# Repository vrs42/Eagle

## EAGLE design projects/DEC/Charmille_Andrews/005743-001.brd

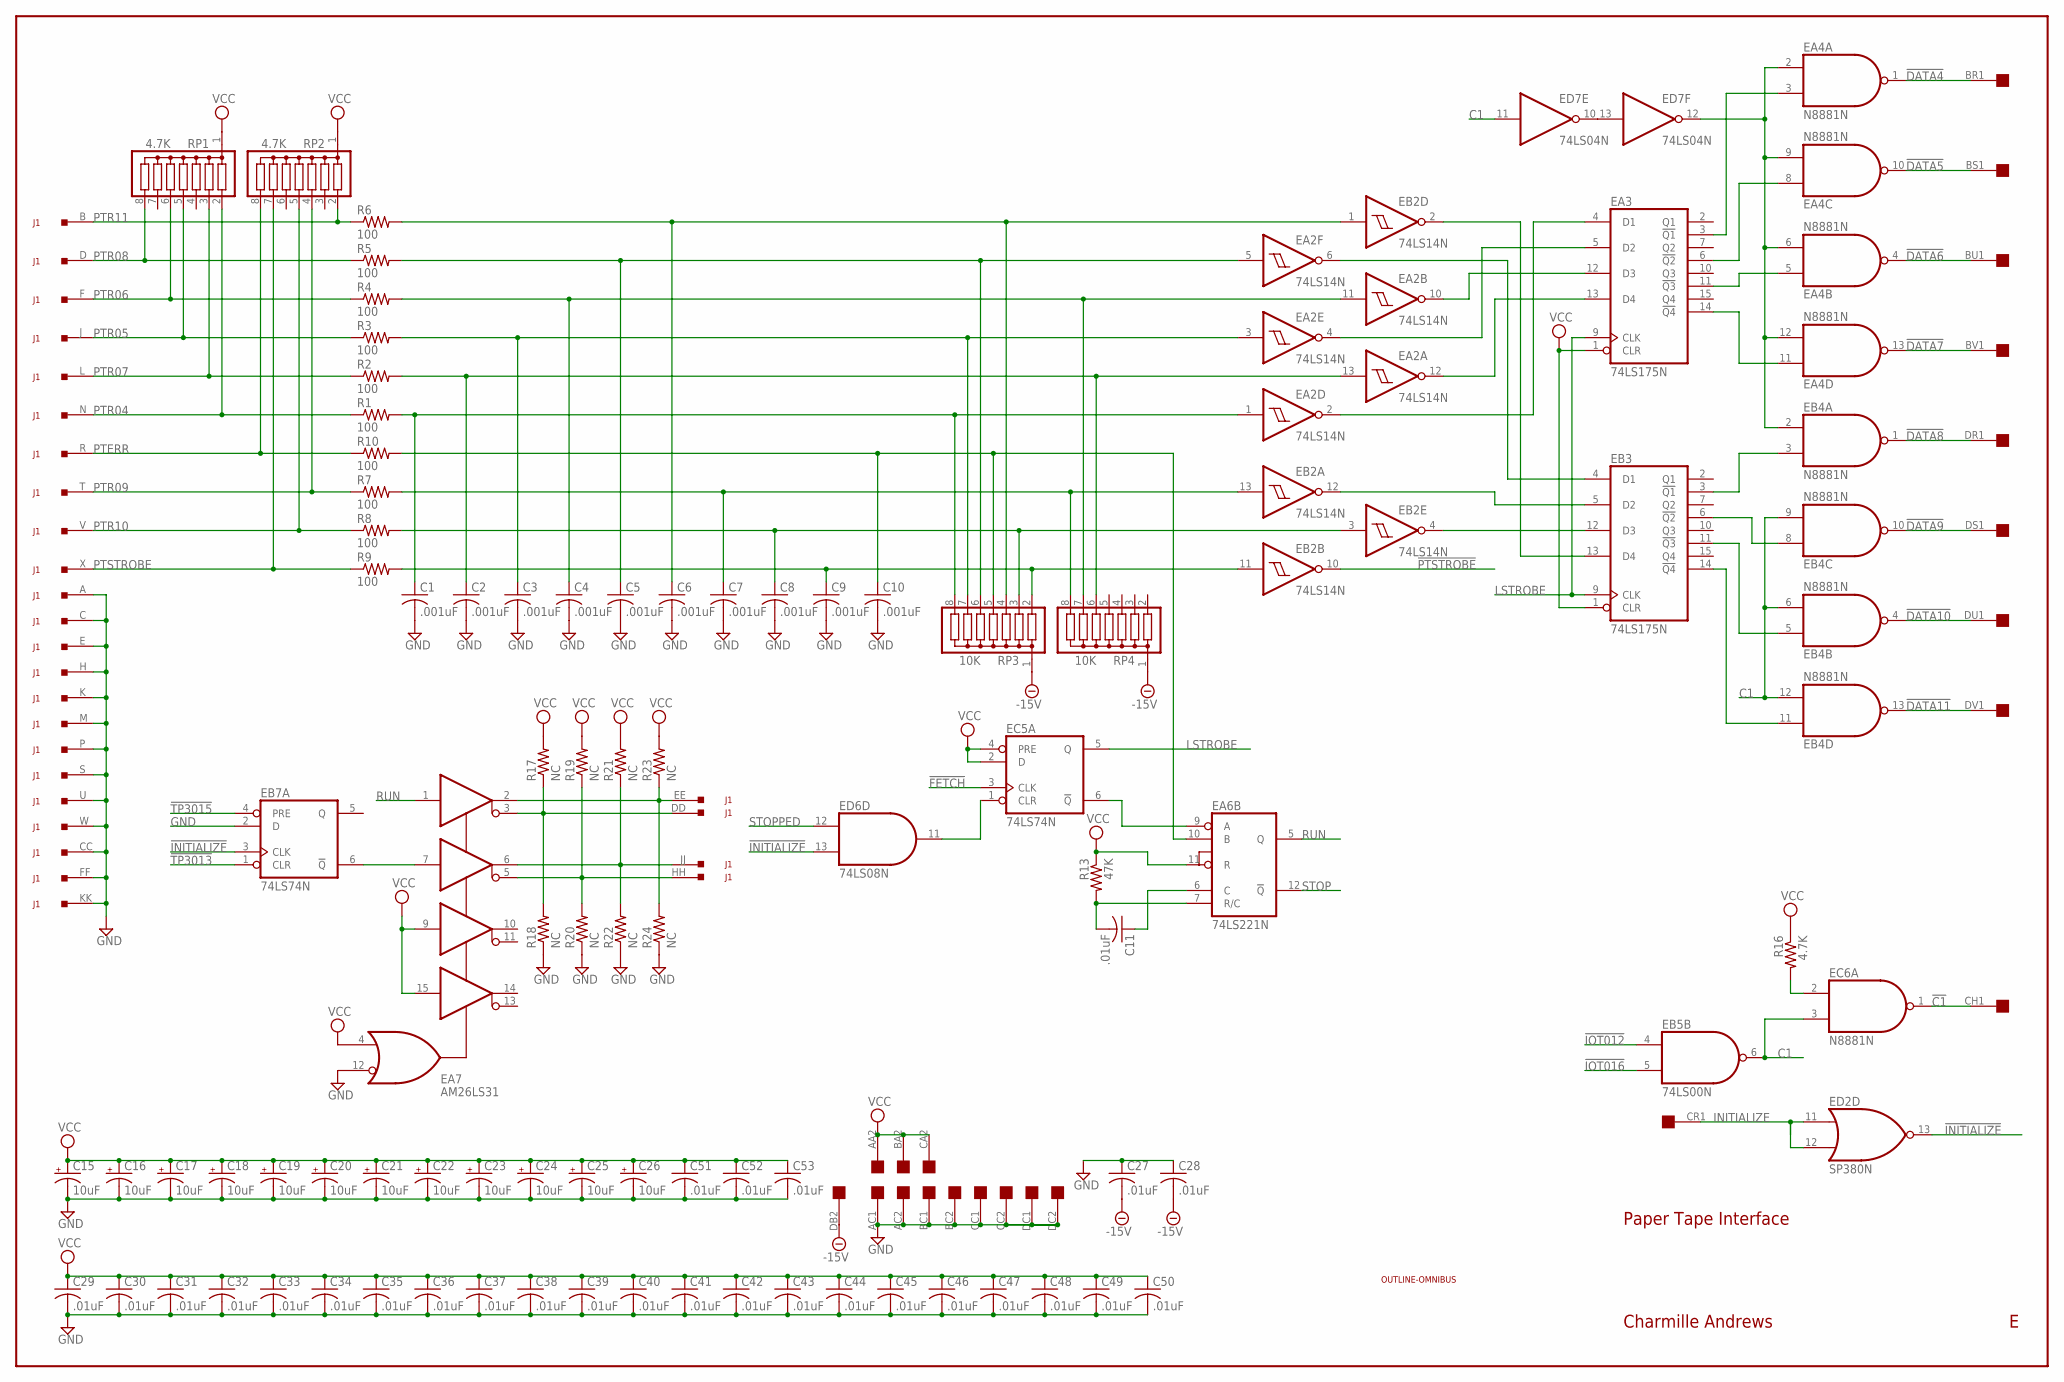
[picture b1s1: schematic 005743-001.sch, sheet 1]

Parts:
C1, C2, C3, C4, C5, C6, C7, C8, C9, C10: .001uF; C050-025X075
C11, C27, C28, C29, C30, C31, C32, C33, C34, C35, C36, C37, C38, C39, C40, C41, C42, C43, C44, C45, C46, C47, C48, C49, C50, C51, C52, C53: .01uF; C050-025X075
C15, C16, C17, C18, C19, C20, C21, C22, C23, C24, C25, C26: 10uF; E15-5
EA2: 74LS14N; DIL14
EA3: 74LS175N; DIL16
EA4: N8881N; DIL14
EA6: 74LS221N; DIL16
EA7: AM26LS31; DIL16
EB2: 74LS14N; DIL14
EB3: 74LS175N; DIL16
EB4: N8881N; DIL14
EB5: 74LS00N; DIL14
EB7: 74LS74N; DIL14
EC5: 74LS74N; DIL14
EC6: N8881N; DIL14
ED2: SP380N; DIL14
ED6: 74LS08N; DIL14
ED7: 74LS04N; DIL14
J1: DEC40PINSH; DEC40PINH
R1, R2, R3, R4, R5, R6, R7, R8, R9, R10: 100; 0207/12
R13: 47K; 0207/12
R16: 4.7K; 0207/12
R17, R18, R19, R20, R21, R22, R23, R24: NC; 0207/12
RP1, RP2: 4.7K; SIL8
RP3, RP4: 10K; SIL8
U$1: OUTLINE-OMNIBUS; OMNIBUS
U$2: QUAD; EDGE-CON8

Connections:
!C1: EC6.1 (O), U$2.CH1
!DATA4: EA4.1 (O), U$2.BR1
!DATA5: EA4.10 (O), U$2.BS1
!DATA6: EA4.4 (O), U$2.BU1
!DATA7: EA4.13 (O), U$2.BV1
!DATA8: EB4.1 (O), U$2.DR1
!DATA9: EB4.10 (O), U$2.DS1
!DATA10: EB4.4 (O), U$2.DU1
!DATA11: EB4.13 (O), U$2.DV1
!FETCH: EC5.3 (CLK); also elsewhere on the board
!INITIALIZE: EB7.3 (CLK), ED2.13 (O), ED6.13 (I1); also elsewhere on the board
!IOT012: EB5.4 (I0); also elsewhere on the board
!IOT016: EB5.5 (I1); also elsewhere on the board
!PTSTROBE: EB2.10 (O); also elsewhere on the board
!TP3013: EB7.1 (CLR); also elsewhere on the board
!TP3015: EB7.4 (PRE); also elsewhere on the board
-15V: C27.2, C28.2, RP3.1, RP4.1, U$2.DB2
C1: EB4.6 (I1), EB4.9 (I1), EB4.12 (I1), EB5.6 (O), EC6.3 (I1), ED7.11 (I)
GND: C1.2, C2.2, C3.2, C4.2, C5.2, C6.2, C7.2, C8.2, C9.2, C10.2, C15.-, C16.-, C17.-, C18.-, C19.-, C20.-, C21.-, C22.-, C23.-, C24.-, C25.-, C26.-, C27.1, C28.1, C29.2, C30.2, C31.2, C32.2, C33.2, C34.2, C35.2, C36.2, C37.2, C38.2, C39.2, C40.2, C41.2, C42.2, C43.2, C44.2, C45.2, C46.2, C47.2, C48.2, C49.2, C50.2, C51.2, C52.2, C53.2, EA2.7 (GND), EA3.8 (GND), EA4.7 (GND), EA6.8 (GND), EA7.8 (GND), EA7.12 (!G), EB2.7 (GND), EB3.8 (GND), EB4.7 (GND), EB5.7 (GND), EB7.2 (D), EB7.7 (GND), EC5.7 (GND), EC6.7 (GND), ED2.1 (GND), ED6.7 (GND), ED7.7 (GND), J1.A, J1.C, J1.CC, J1.E, J1.FF, J1.H, J1.K, J1.KK, J1.M, J1.P, J1.S, J1.U, J1.W, R18.1, R20.1, R22.1, R24.1, U$2.AC1, U$2.AC2, U$2.BC1, U$2.BC2, U$2.CC1, U$2.CC2, U$2.DC1, U$2.DC2; also elsewhere on the board
INITIALIZE: ED2.11 (I0), ED2.12 (I1), U$2.CR1
LSTROBE: EA3.9 (CLK), EB3.9 (CLK), EC5.5 (Q); also elsewhere on the board
unnamed: EA4.2 (I0), EA4.6 (I1), EA4.9 (I1), EA4.12 (I1), EB4.2 (I0), ED7.12 (O)
unnamed: EA2.6 (O), EB3.4 (D1)
unnamed: ED7.10 (O), ED7.13 (I)
unnamed: EA7.2 (Y1), J1.EE, R23.1, R24.2
unnamed: EA7.3 (Z1), J1.DD, R17.1, R18.2
unnamed: EC5.1 (CLR), ED6.11 (O)
unnamed: EA7.5 (Z2), J1.HH, R19.1, R20.2
unnamed: EA7.6 (Y2), J1.JJ, R21.1, R22.2
unnamed: EB2.2 (O), EB3.13 (D4)
unnamed: EA2.12 (O), EA3.13 (D4)
unnamed: EA7.7 (A2), EB7.6 (!Q)
unnamed: EA2.10 (O), EA3.12 (D3)
unnamed: EA3.6 (!Q2), EA4.8 (I0)
unnamed: EA6.9 (A), EC5.6 (!Q)
unnamed: EC6.2 (I0), R16.2
unnamed: C10.1, EA6.10 (B), R10.2, RP3.5
unnamed: C11.1, EA6.6 (C)
unnamed: EA2.2 (O), EA3.4 (D1)
unnamed: EA3.3 (!Q1), EA4.3 (I1)
unnamed: EA3.14 (!Q4), EA4.11 (I0)
unnamed: C11.2, EA6.7 (R/C), R13.2
unnamed: EB3.14 (!Q4), EB4.11 (I0)
unnamed: EB3.6 (!Q2), EB4.8 (I0)
unnamed: EB3.11 (!Q3), EB4.5 (I0)
unnamed: EB3.3 (!Q1), EB4.3 (I1)
unnamed: EB2.12 (O), EB3.5 (D2)
unnamed: EB2.4 (O), EB3.12 (D3)
unnamed: C7.1, EB2.13 (I), R7.2, RP4.8
unnamed: C8.1, EB2.3 (I), R8.2, RP3.3
unnamed: C6.1, EB2.1 (I), R6.2, RP3.4
unnamed: C9.1, EB2.11 (I), R9.2, RP3.2
unnamed: EA3.11 (!Q3), EA4.5 (I0)
unnamed: EA2.4 (O), EA3.5 (D2)
unnamed: C2.1, EA2.13 (I), R2.2, RP4.6
unnamed: C5.1, EA2.5 (I), R5.2, RP3.6
unnamed: C3.1, EA2.3 (I), R3.2, RP3.7
unnamed: C1.1, EA2.1 (I), R1.2, RP3.8
unnamed: C4.1, EA2.11 (I), R4.2, RP4.7
PTERR: J1.R, R10.1, RP2.8
PTR04: J1.N, R1.1, RP1.2
PTR05: J1.J, R3.1, RP1.5
PTR06: J1.F, R4.1, RP1.6
PTR07: J1.L, R2.1, RP1.3
PTR08: J1.D, R5.1, RP1.8
PTR09: J1.T, R7.1, RP2.4
PTR10: J1.V, R8.1, RP2.5
PTR11: J1.B, R6.1, RP2.2
PTSTROBE: J1.X, R9.1, RP2.7
RUN: EA6.5 (Q), EA7.1 (A1); also elsewhere on the board
STOP: EA6.12 (!Q); also elsewhere on the board
STOPPED: ED6.12 (I0); also elsewhere on the board
VCC: C15.+, C16.+, C17.+, C18.+, C19.+, C20.+, C21.+, C22.+, C23.+, C24.+, C25.+, C26.+, C29.1, C30.1, C31.1, C32.1, C33.1, C34.1, C35.1, C36.1, C37.1, C38.1, C39.1, C40.1, C41.1, C42.1, C43.1, C44.1, C45.1, C46.1, C47.1, C48.1, C49.1, C50.1, C51.1, C52.1, C53.1, EA2.14 (VCC), EA3.1 (CLR), EA3.16 (VCC), EA4.14 (VCC), EA6.11 (R), EA6.16 (VCC), EA7.4 (G), EA7.9 (A3), EA7.15 (A4), EA7.16 (VCC), EB2.14 (VCC), EB3.1 (CLR), EB3.16 (VCC), EB4.14 (VCC), EB5.14 (VCC), EB7.14 (VCC), EC5.2 (D), EC5.4 (PRE), EC5.14 (VCC), EC6.14 (VCC), ED2.8 (VCC), ED6.14 (VCC), ED7.14 (VCC), R13.1, R16.1, R17.2, R19.2, R21.2, R23.2, RP1.1, RP2.1, U$2.AA2, U$2.BA2, U$2.CA2; also elsewhere on the board

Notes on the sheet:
Paper Tape Interface
Charmille Andrews

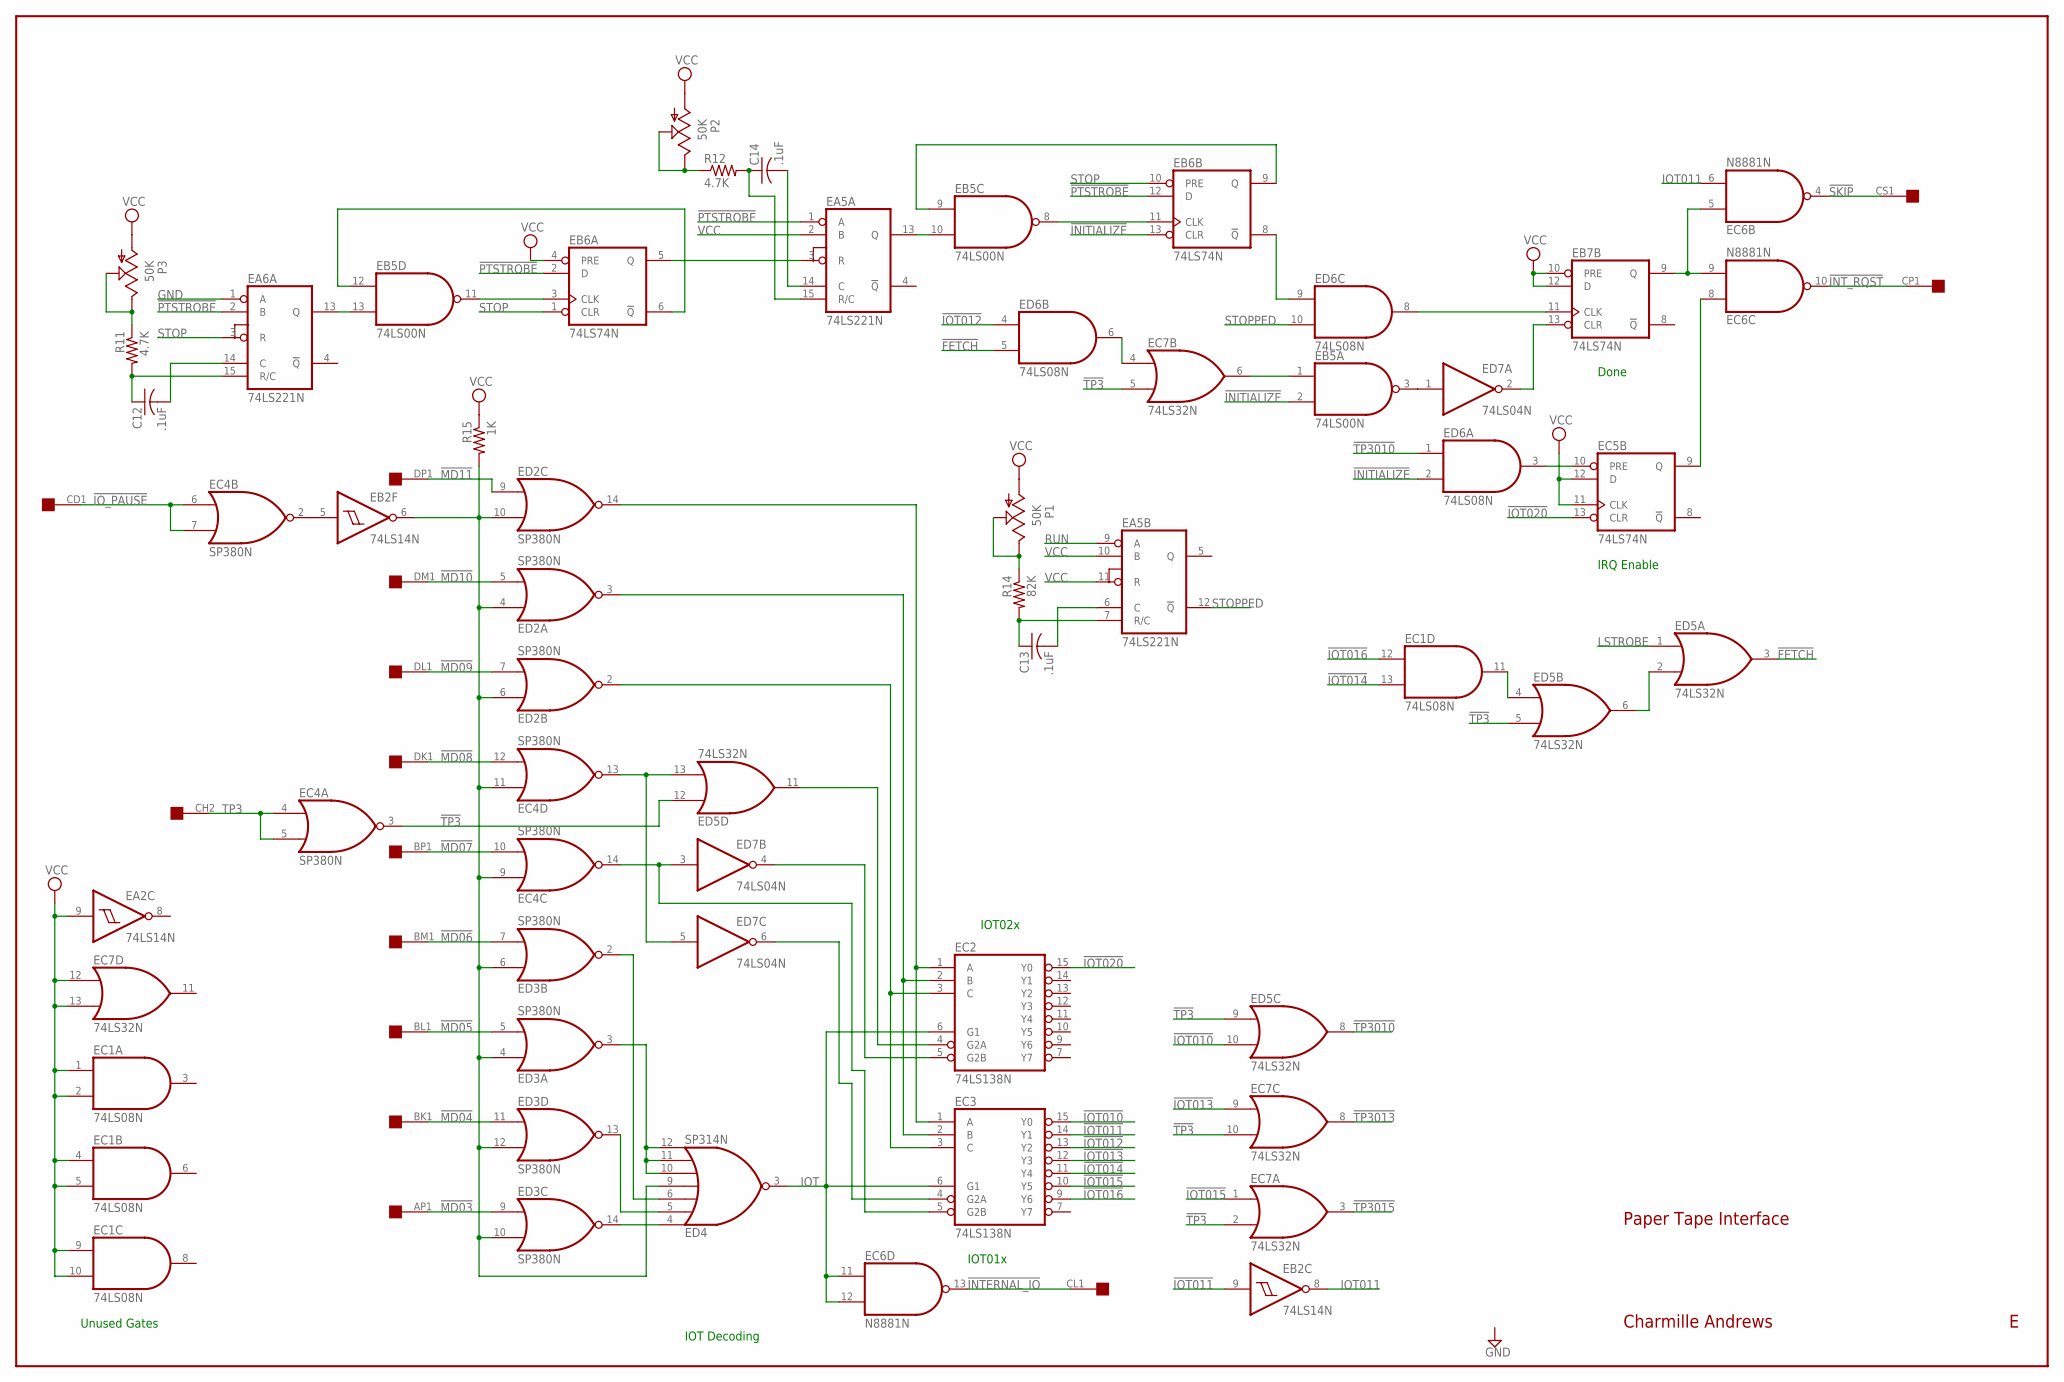
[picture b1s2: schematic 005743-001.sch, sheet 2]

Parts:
C12, C13, C14: .1uF; C150-054X183
EA2: 74LS14N; DIL14
EA5, EA6: 74LS221N; DIL16
EB2: 74LS14N; DIL14
EB5: 74LS00N; DIL14
EB6, EB7: 74LS74N; DIL14
EC1: 74LS08N; DIL14
EC2, EC3: 74LS138N; DIL16
EC4: SP380N; DIL14
EC5: 74LS74N; DIL14
EC6: N8881N; DIL14
EC7: 74LS32N; DIL14
ED2, ED3: SP380N; DIL14
ED4: SP314N; DIL14
ED5: 74LS32N; DIL14
ED6: 74LS08N; DIL14
ED7: 74LS04N; DIL14
P1, P2, P3: 50K; SP19L
R11, R12: 4.7K; 0207/12
R14: 82K; 0207/12
R15: 1K; 0207/12
U$2: QUAD; EDGE-CON8

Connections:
!FETCH: ED5.3 (O), ED6.5 (I1); also elsewhere on the board
!INITIALIZE: EB5.2 (I1), EB6.13 (CLR), ED6.2 (I1); also elsewhere on the board
!INTERNAL_IO: EC6.13 (O), U$2.CL1
!INT_RQST: EC6.10 (O), U$2.CP1
!IOT010: EC3.15 (Y0), ED5.10 (I1)
!IOT011: EB2.9 (I), EC3.14 (Y1)
!IOT012: EC3.13 (Y2), ED6.4 (I0); also elsewhere on the board
!IOT013: EC3.12 (Y3), EC7.9 (I0)
!IOT014: EC1.13 (I1), EC3.11 (Y4)
!IOT015: EC3.10 (Y5), EC7.1 (I0)
!IOT016: EC1.12 (I0), EC3.9 (Y6); also elsewhere on the board
!IOT020: EC2.15 (Y0), EC5.13 (CLR)
!IO_PAUSE: EC4.6 (I0), EC4.7 (I1), U$2.CD1
!MD03: ED3.9 (I0), U$2.AP1
!MD04: ED3.11 (I0), U$2.BK1
!MD05: ED3.5 (I1), U$2.BL1
!MD06: ED3.7 (I1), U$2.BM1
!MD07: EC4.10 (I1), U$2.BP1
!MD08: EC4.12 (I1), U$2.DK1
!MD09: ED2.7 (I1), U$2.DL1
!MD10: ED2.5 (I1), U$2.DM1
!MD11: ED2.9 (I0), U$2.DP1
!PTSTROBE: EA5.1 (A), EA6.2 (B), EB6.2 (D), EB6.12 (D); also elsewhere on the board
!SKIP: EC6.4 (O), U$2.CS1
!TP3: EC4.3 (O), EC7.2 (I1), EC7.5 (I1), EC7.10 (I1), ED5.5 (I1), ED5.9 (I0), ED5.12 (I0)
!TP3010: ED5.8 (O), ED6.1 (I0)
!TP3013: EC7.8 (O); also elsewhere on the board
!TP3015: EC7.3 (O); also elsewhere on the board
GND: EA2.7 (GND), EA5.8 (GND), EA6.1 (A), EA6.8 (GND), EB2.7 (GND), EB5.7 (GND), EB6.7 (GND), EB7.7 (GND), EC1.7 (GND), EC2.8 (GND), EC3.8 (GND), EC4.1 (GND), EC5.7 (GND), EC6.7 (GND), EC7.7 (GND), ED2.1 (GND), ED3.1 (GND), ED4.1 (GND), ED5.7 (GND), ED6.7 (GND), ED7.7 (GND); also elsewhere on the board
IOT: EC2.6 (G1), EC3.6 (G1), EC6.11 (I0), EC6.12 (I1), ED4.3 (O)
IOT011: EB2.8 (O), EC6.6 (I1)
LSTROBE: ED5.1 (I0); also elsewhere on the board
unnamed: EB5.3 (O), ED7.1 (I)
unnamed: EC4.13 (O), ED5.13 (I1), ED7.5 (I)
unnamed: EC3.5 (G2B), EC4.14 (O), ED7.3 (I)
unnamed: EB7.13 (CLR), ED7.2 (O)
unnamed: EC3.4 (G2A), ED7.6 (O)
unnamed: EB7.11 (CLK), ED6.8 (O)
unnamed: EB6.8 (!Q), ED6.9 (I0)
unnamed: EC5.10 (PRE), ED6.3 (O)
unnamed: EC7.4 (I0), ED6.6 (O)
unnamed: C12.2, EA6.14 (C)
unnamed: C14.1, EA5.15 (R/C), R12.2
unnamed: EA5.3 (R), EB6.5 (Q)
unnamed: EC1.11 (O), ED5.4 (I0)
unnamed: ED5.2 (I1), ED5.6 (O)
unnamed: EA6.13 (Q), EB5.13 (I1)
unnamed: EC2.4 (G2A), ED5.11 (O)
unnamed: ED3.14 (O), ED4.4 (I0)
unnamed: ED3.3 (O), ED4.10 (I4), ED4.11 (I5), ED4.12 (I6)
unnamed: EB2.6 (O), EC4.9 (I0), EC4.11 (I0), ED2.4 (I0), ED2.6 (I0), ED2.10 (I1), ED3.4 (I0), ED3.6 (I0), ED3.10 (I1), ED3.12 (I1), ED4.9 (I3), R15.2
unnamed: ED3.2 (O), ED4.6 (I2)
unnamed: ED3.13 (O), ED4.5 (I1)
unnamed: EB2.5 (I), EC4.2 (O)
unnamed: EC2.1 (A), EC3.1 (A), ED2.14 (O)
unnamed: EC2.5 (G2B), ED7.4 (O)
unnamed: EC2.2 (B), EC3.2 (B), ED2.3 (O)
unnamed: EC2.3 (C), EC3.3 (C), ED2.2 (O)
unnamed: EB7.9 (Q), EC6.5 (I0), EC6.9 (I1)
unnamed: EC5.9 (Q), EC6.8 (I0)
unnamed: EB5.1 (I0), EC7.6 (O)
unnamed: EB5.8 (O), EB6.11 (CLK)
unnamed: EB5.9 (I0), EB6.9 (Q)
unnamed: EB5.11 (O), EB6.3 (CLK)
unnamed: EB5.12 (I0), EB6.6 (!Q)
unnamed: EA5.13 (Q), EB5.10 (I1)
unnamed: C12.1, EA6.15 (R/C), R11.2
unnamed: C13.2, EA5.6 (C)
unnamed: C13.1, EA5.7 (R/C), R14.2
unnamed: C14.2, EA5.14 (C)
unnamed: P1.E, P1.S, R14.1
unnamed: P2.E, P2.S, R12.1
unnamed: P3.E, P3.S, R11.1
RUN: EA5.9 (A); also elsewhere on the board
STOP: EA6.3 (R), EB6.1 (CLR), EB6.10 (PRE); also elsewhere on the board
STOPPED: EA5.12 (!Q), ED6.10 (I1); also elsewhere on the board
TP3: EC4.4 (I0), EC4.5 (I1), U$2.CH2
VCC: EA2.9 (I), EA2.14 (VCC), EA5.2 (B), EA5.10 (B), EA5.11 (R), EA5.16 (VCC), EA6.16 (VCC), EB2.14 (VCC), EB5.14 (VCC), EB6.4 (PRE), EB6.14 (VCC), EB7.10 (PRE), EB7.12 (D), EB7.14 (VCC), EC1.1 (I0), EC1.2 (I1), EC1.4 (I0), EC1.5 (I1), EC1.9 (I0), EC1.10 (I1), EC1.14 (VCC), EC2.16 (VCC), EC3.16 (VCC), EC4.8 (VCC), EC5.11 (CLK), EC5.12 (D), EC5.14 (VCC), EC6.14 (VCC), EC7.12 (I0), EC7.13 (I1), EC7.14 (VCC), ED2.8 (VCC), ED3.8 (VCC), ED4.8 (VCC), ED5.14 (VCC), ED6.14 (VCC), ED7.14 (VCC), P1.A, P2.A, P3.A, R15.1; also elsewhere on the board

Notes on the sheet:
IOT02x
IOT01x
IOT Decoding
Unused Gates
IRQ Enable
Done
Paper Tape Interface
Charmille Andrews

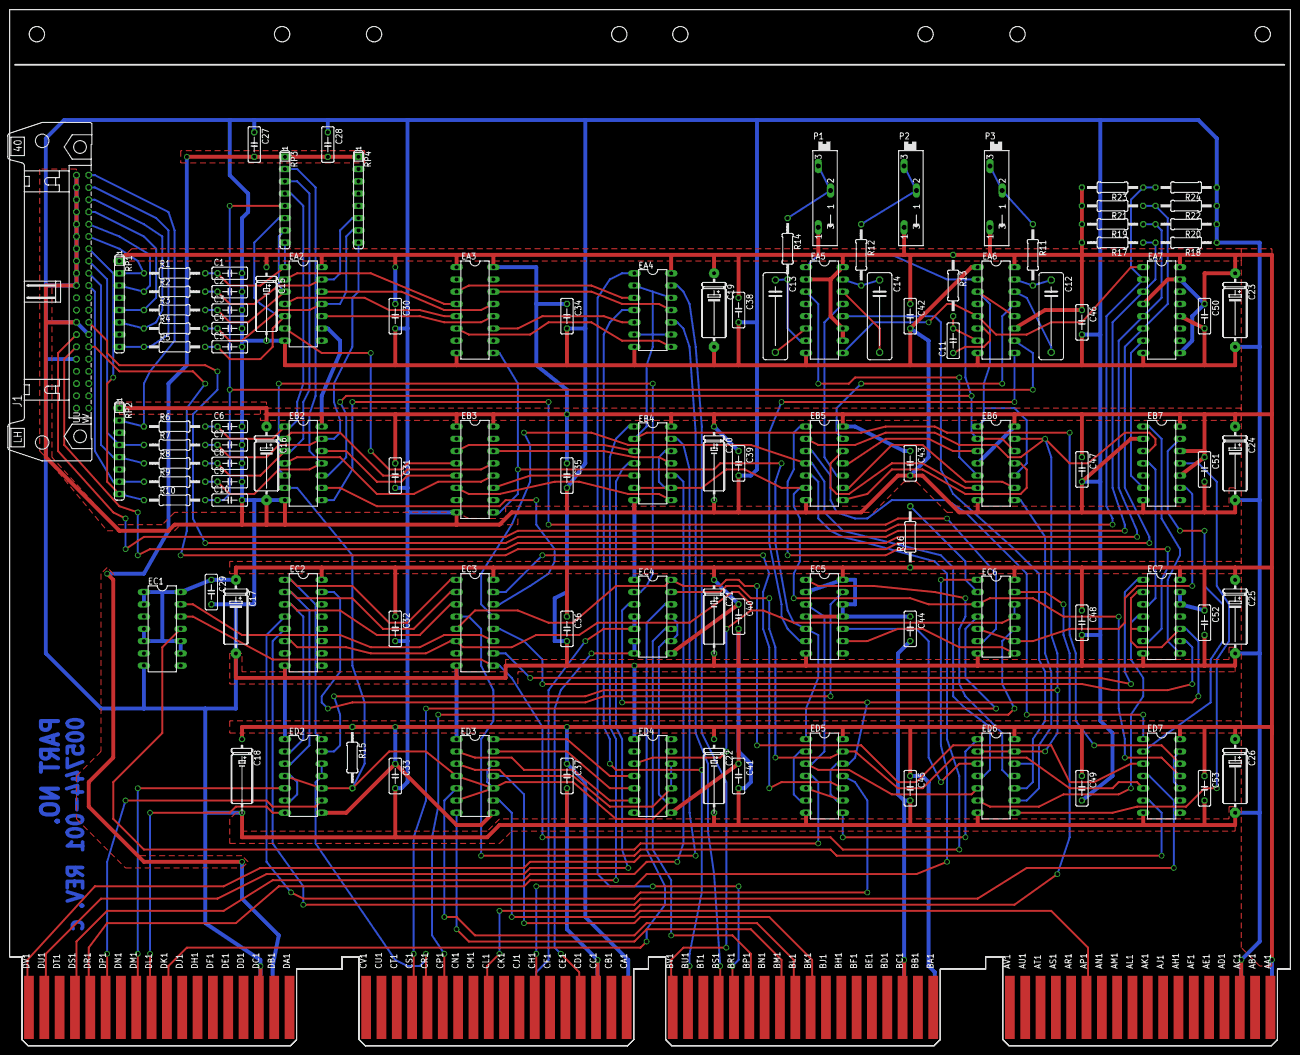
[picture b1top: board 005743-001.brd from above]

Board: 2 copper layers, 265.3 x 214.6 mm, 112 parts (0 on the bottom side), 138 nets.

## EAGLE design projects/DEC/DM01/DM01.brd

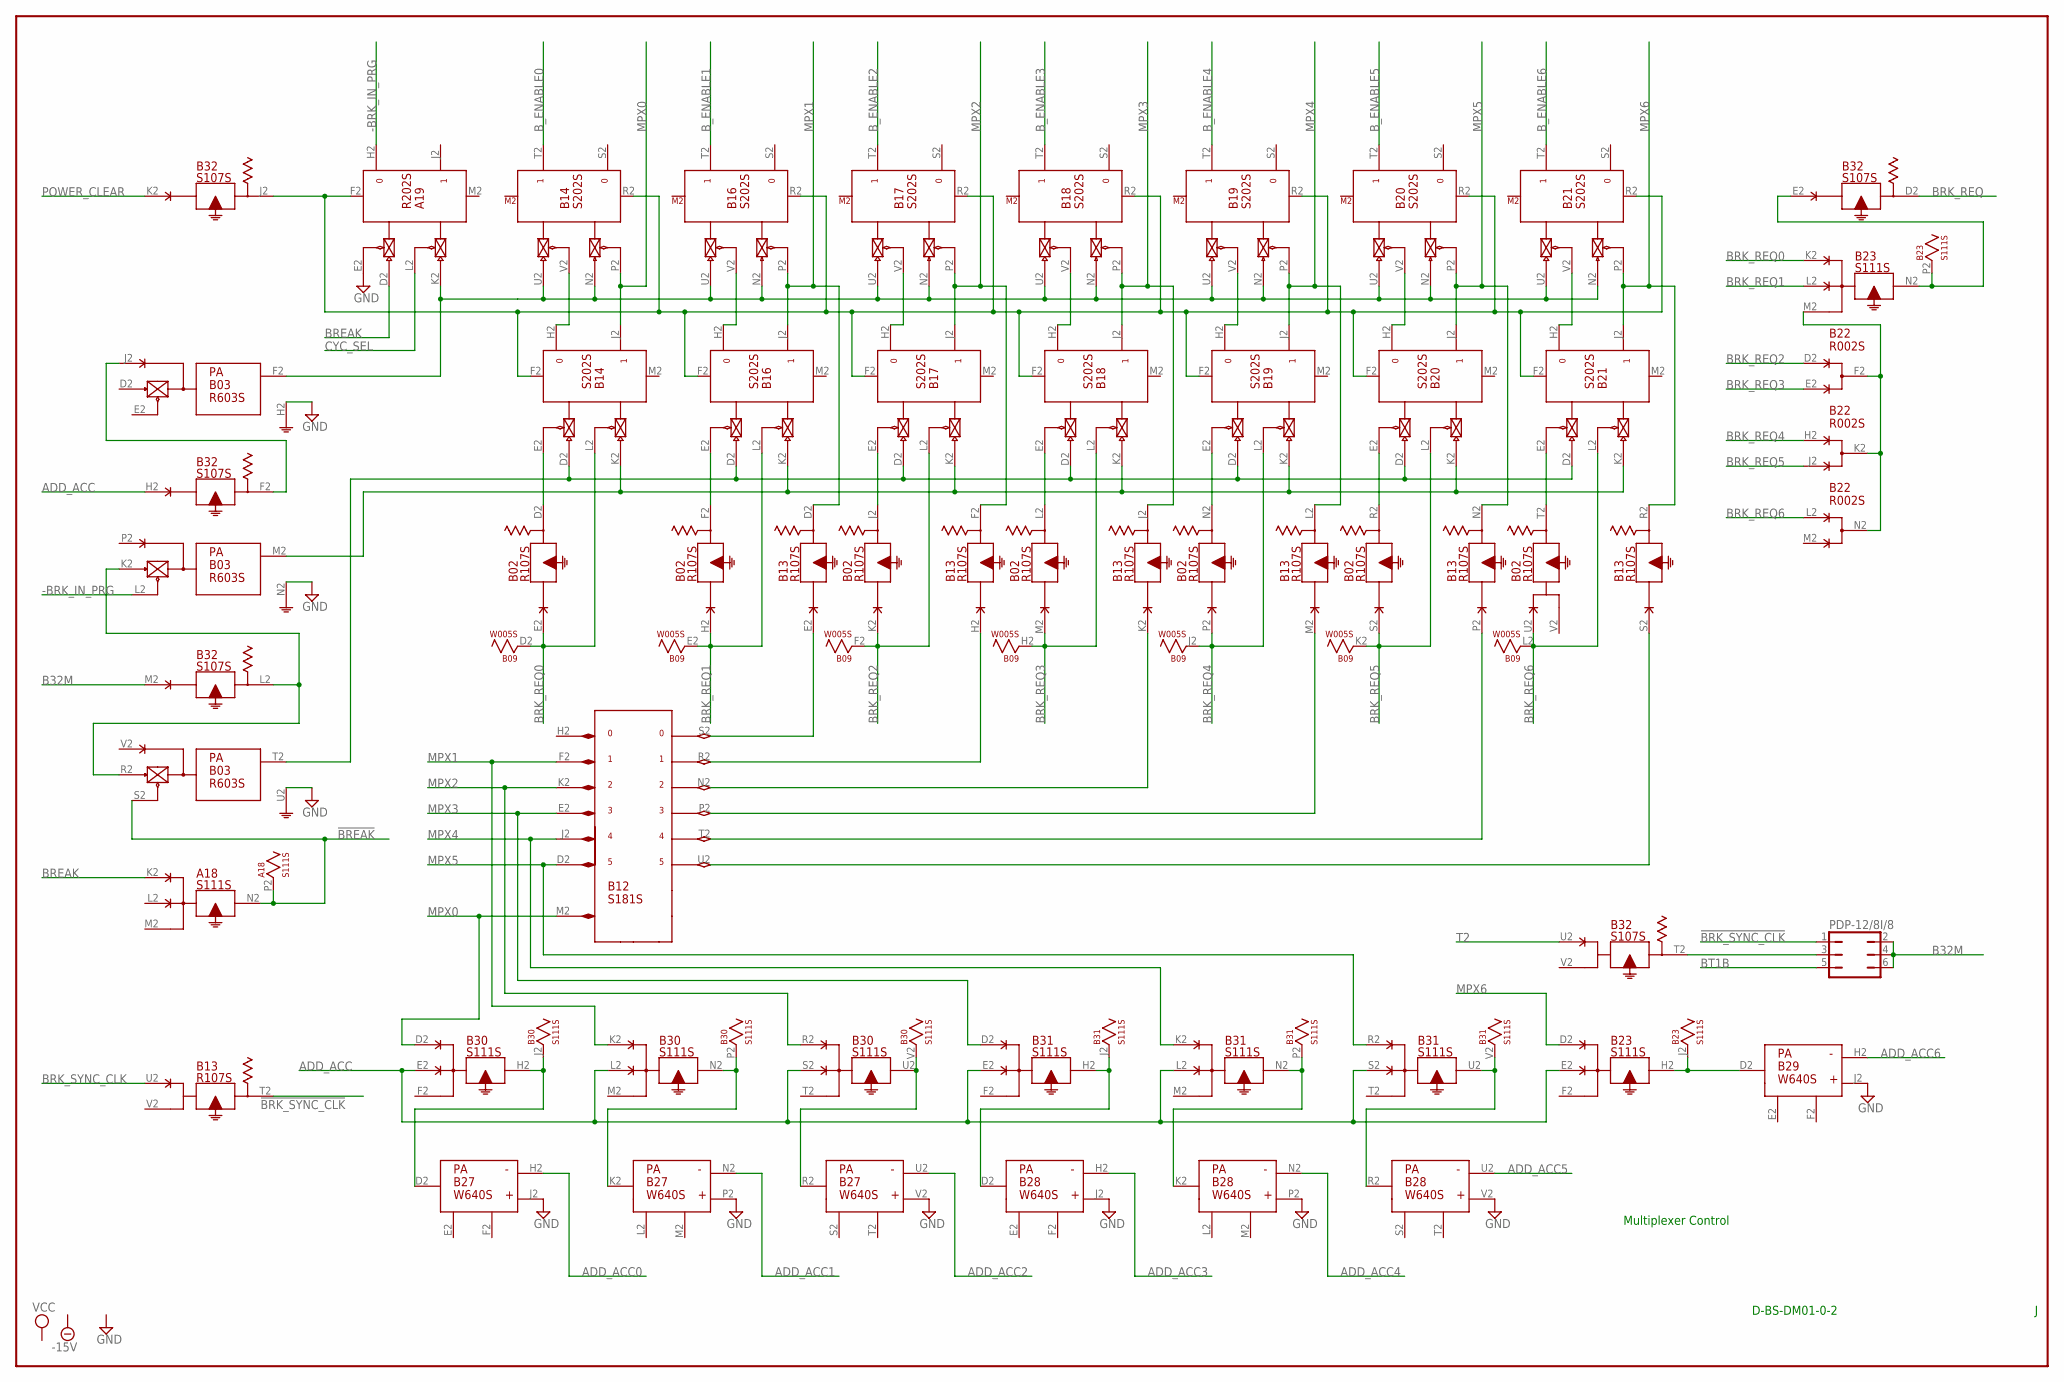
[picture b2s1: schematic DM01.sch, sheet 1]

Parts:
A18: S111S; H807S
A19: R202S; H807S
B02, B13: R107S; H807S
B03: R603S; H807S
B09: W005S; H807S
B12: S181S; H807S
B14, B16, B17, B18, B19, B20, B21: S202S; H807S
B22: R002S; H807S
B23, B30, B31: S111S; H807S
B27, B28, B29: W640S; H807S
B32: S107S; H807S
PDP-12/8I/8: JP3Q

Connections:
!BREAK: A18.N2, A18.P2, B03.S2 (EN0)
!BRK_SYNC_CLK: B13.T2, PDP-12/8I/8.1
-15V: A18.B2 (-15V), A19.B2 (-15V), B02.B2 (-15V), B03.B2 (-15V), B09.B2 (-15V), B12.B2 (-15V), B13.B2 (-15V), B14.B2 (-15V), B16.B2 (-15V), B17.B2 (-15V), B18.B2 (-15V), B19.B2 (-15V), B20.B2 (-15V), B21.B2 (-15V), B22.B2 (-15V), B23.B2 (-15V), B27.B2 (-15V), B28.B2 (-15V), B29.B2 (-15V), B30.B2 (-15V), B31.B2 (-15V), B32.B2 (-15V); also elsewhere on the board
-BRK_IN_PRG: A19.H2 (0), B03.L2 (EN0)
ADD_ACC: B23.E2, B30.E2, B30.L2, B30.S2, B31.E2, B31.L2, B31.S2, B32.H2; also elsewhere on the board
ADD_ACC0: B27.H2 (H); also elsewhere on the board
ADD_ACC1: B27.N2 (H); also elsewhere on the board
ADD_ACC2: B27.U2 (H); also elsewhere on the board
ADD_ACC3: B28.H2 (H); also elsewhere on the board
ADD_ACC4: B28.N2 (H); also elsewhere on the board
ADD_ACC5: B28.U2 (H); also elsewhere on the board
ADD_ACC6: B29.H2 (H); also elsewhere on the board
B32M: B32.M2, PDP-12/8I/8.2, PDP-12/8I/8.4, PDP-12/8I/8.6
BREAK: A18.K2, A19.D2 (PU0); also elsewhere on the board
BRK_REQ: B32.D2; also elsewhere on the board
BRK_REQ0: B02.E2, B09.D2, B14.L2 (EN1), B23.K2; also elsewhere on the board
BRK_REQ1: B02.H2, B09.E2, B16.L2 (EN1), B23.L2; also elsewhere on the board
BRK_REQ2: B02.K2, B09.F2, B17.L2 (EN1), B22.D2 (D); also elsewhere on the board
BRK_REQ3: B02.M2, B09.H2, B18.L2 (EN1), B22.E2 (E); also elsewhere on the board
BRK_REQ4: B02.P2, B09.J2, B19.L2 (EN1), B22.H2 (D); also elsewhere on the board
BRK_REQ5: B02.S2, B09.K2, B20.L2 (EN1), B22.J2 (E); also elsewhere on the board
BRK_REQ6: B02.U2, B09.L2, B21.L2 (EN1), B22.L2 (D); also elsewhere on the board
BRK_SYNC_CLK: B13.U2; also elsewhere on the board
BT1B: PDP-12/8I/8.5; also elsewhere on the board
B_ENABLE0: B14.T2 (1); also elsewhere on the board
B_ENABLE1: B16.T2 (1); also elsewhere on the board
B_ENABLE2: B17.T2 (1); also elsewhere on the board
B_ENABLE3: B18.T2 (1); also elsewhere on the board
B_ENABLE4: B19.T2 (1); also elsewhere on the board
B_ENABLE5: B20.T2 (1); also elsewhere on the board
B_ENABLE6: B21.T2 (1); also elsewhere on the board
CYC_SEL: A19.L2 (EN1); also elsewhere on the board
GND: A18.C2 (GND), A19.C2 (GND), A19.E2 (EN0), B02.C2 (GND), B03.C2 (GND), B03.H2 (G), B03.N2 (G), B03.U2 (G), B09.C2 (GND), B12.C2 (GND), B13.C2 (GND), B14.C2 (GND), B16.C2 (GND), B17.C2 (GND), B18.C2 (GND), B19.C2 (GND), B20.C2 (GND), B21.C2 (GND), B22.C2 (GND), B23.C2 (GND), B27.C2 (GND), B27.J2 (J), B27.P2 (J), B27.V2 (J), B28.C2 (GND), B28.J2 (J), B28.P2 (J), B28.V2 (J), B29.C2 (GND), B29.J2 (J), B30.C2 (GND), B31.C2 (GND), B32.C2 (GND); also elsewhere on the board
MPX0: B12.M2 (M), B14.J2 (1), B14.P2 (EN0), B30.D2; also elsewhere on the board
MPX1: B12.F2 (F), B13.D2, B16.J2 (1), B16.P2 (EN0), B30.K2; also elsewhere on the board
MPX2: B12.K2 (K), B13.F2, B17.J2 (1), B17.P2 (EN0), B30.R2; also elsewhere on the board
MPX3: B12.E2 (E), B13.J2, B18.J2 (1), B18.P2 (EN0), B31.D2; also elsewhere on the board
MPX4: B12.J2 (J), B13.L2, B19.J2 (1), B19.P2 (EN0), B31.K2; also elsewhere on the board
MPX5: B12.D2 (D), B13.N2, B20.J2 (1), B20.P2 (EN0), B31.R2; also elsewhere on the board
MPX6: B13.R2, B21.J2 (1), B21.P2 (EN0), B23.D2; also elsewhere on the board
unnamed: A19.K2 (PU1), B03.F2 (O), B14.N2 (PU0), B14.U2 (PU1), B16.N2 (PU0), B16.U2 (PU1), B17.N2 (PU0), B17.U2 (PU1), B18.N2 (PU0), B18.U2 (PU1), B19.N2 (PU0), B19.U2 (PU1), B20.N2 (PU0), B20.U2 (PU1), B21.N2 (PU0), B21.U2 (PU1)
unnamed: A19.F2 (RESET), B14.F2 (RESET), B14.R2 (RESET), B16.F2 (RESET), B16.R2 (RESET), B17.F2 (RESET), B17.R2 (RESET), B18.F2 (RESET), B18.R2 (RESET), B19.F2 (RESET), B19.R2 (RESET), B20.F2 (RESET), B20.R2 (RESET), B21.F2 (RESET), B21.R2 (RESET), B32.J2
unnamed: B03.J2, B32.F2
unnamed: B32.T2, PDP-12/8I/8.3
unnamed: B03.K2 (PU0), B03.R2 (PU0), B32.L2
unnamed: B03.M2 (O), B14.K2 (PU1), B16.K2 (PU1), B17.K2 (PU1), B18.K2 (PU1), B19.K2 (PU1), B20.K2 (PU1), B21.K2 (PU1)
unnamed: B14.H2 (0), B14.V2 (EN1)
unnamed: B16.H2 (0), B16.V2 (EN1)
unnamed: B17.H2 (0), B17.V2 (EN1)
unnamed: B18.H2 (0), B18.V2 (EN1)
unnamed: B19.H2 (0), B19.V2 (EN1)
unnamed: B20.H2 (0), B20.V2 (EN1)
unnamed: B21.H2 (0), B21.V2 (EN1)
unnamed: B23.N2, B23.P2, B32.E2
unnamed: B22.F2 (F), B22.K2 (F), B22.N2 (F), B23.M2
unnamed: B02.D2, B14.E2 (EN0)
unnamed: B02.F2, B16.E2 (EN0)
unnamed: B02.J2, B17.E2 (EN0)
unnamed: B02.L2, B18.E2 (EN0)
unnamed: B02.N2, B19.E2 (EN0)
unnamed: B02.R2, B20.E2 (EN0)
unnamed: B02.T2, B21.E2 (EN0)
unnamed: B27.D2 (D), B30.H2, B30.J2
unnamed: B03.T2 (O), B14.D2 (PU0), B16.D2 (PU0), B17.D2 (PU0), B18.D2 (PU0), B19.D2 (PU0), B20.D2 (PU0), B21.D2 (PU0)
unnamed: B27.K2 (D), B30.N2, B30.P2
unnamed: B27.R2 (D), B30.U2, B30.V2
unnamed: B12.S2 (S), B13.E2
unnamed: B12.R2 (R), B13.H2
unnamed: B12.N2 (N), B13.K2
unnamed: B12.P2, B13.M2
unnamed: B12.T2 (T), B13.P2
unnamed: B12.U2 (U), B13.S2
unnamed: B28.D2 (D), B31.H2, B31.J2
unnamed: B28.K2 (D), B31.N2, B31.P2
unnamed: B28.R2 (D), B31.U2, B31.V2
unnamed: B23.H2, B23.J2, B29.D2 (D)
POWER_CLEAR: B32.K2; also elsewhere on the board
T2: B32.U2; also elsewhere on the board
VCC: A18.A2 (VCC), A19.A2 (VCC), B02.A2 (VCC), B03.A2 (VCC), B09.A2 (VCC), B12.A2 (VCC), B13.A2 (VCC), B14.A2 (VCC), B16.A2 (VCC), B17.A2 (VCC), B18.A2 (VCC), B19.A2 (VCC), B20.A2 (VCC), B21.A2 (VCC), B22.A2 (VCC), B23.A2 (VCC), B27.A2 (VCC), B28.A2 (VCC), B29.A2 (VCC), B30.A2 (VCC), B31.A2 (VCC), B32.A2 (VCC); also elsewhere on the board

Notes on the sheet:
Multiplexer Control
D-BS-DM01-0-2
